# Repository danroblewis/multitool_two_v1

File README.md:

This was originally supposed to be 3 modules mashed together

But I'm bad at noise generator circuits

So I made a beat sequencer with flipflops

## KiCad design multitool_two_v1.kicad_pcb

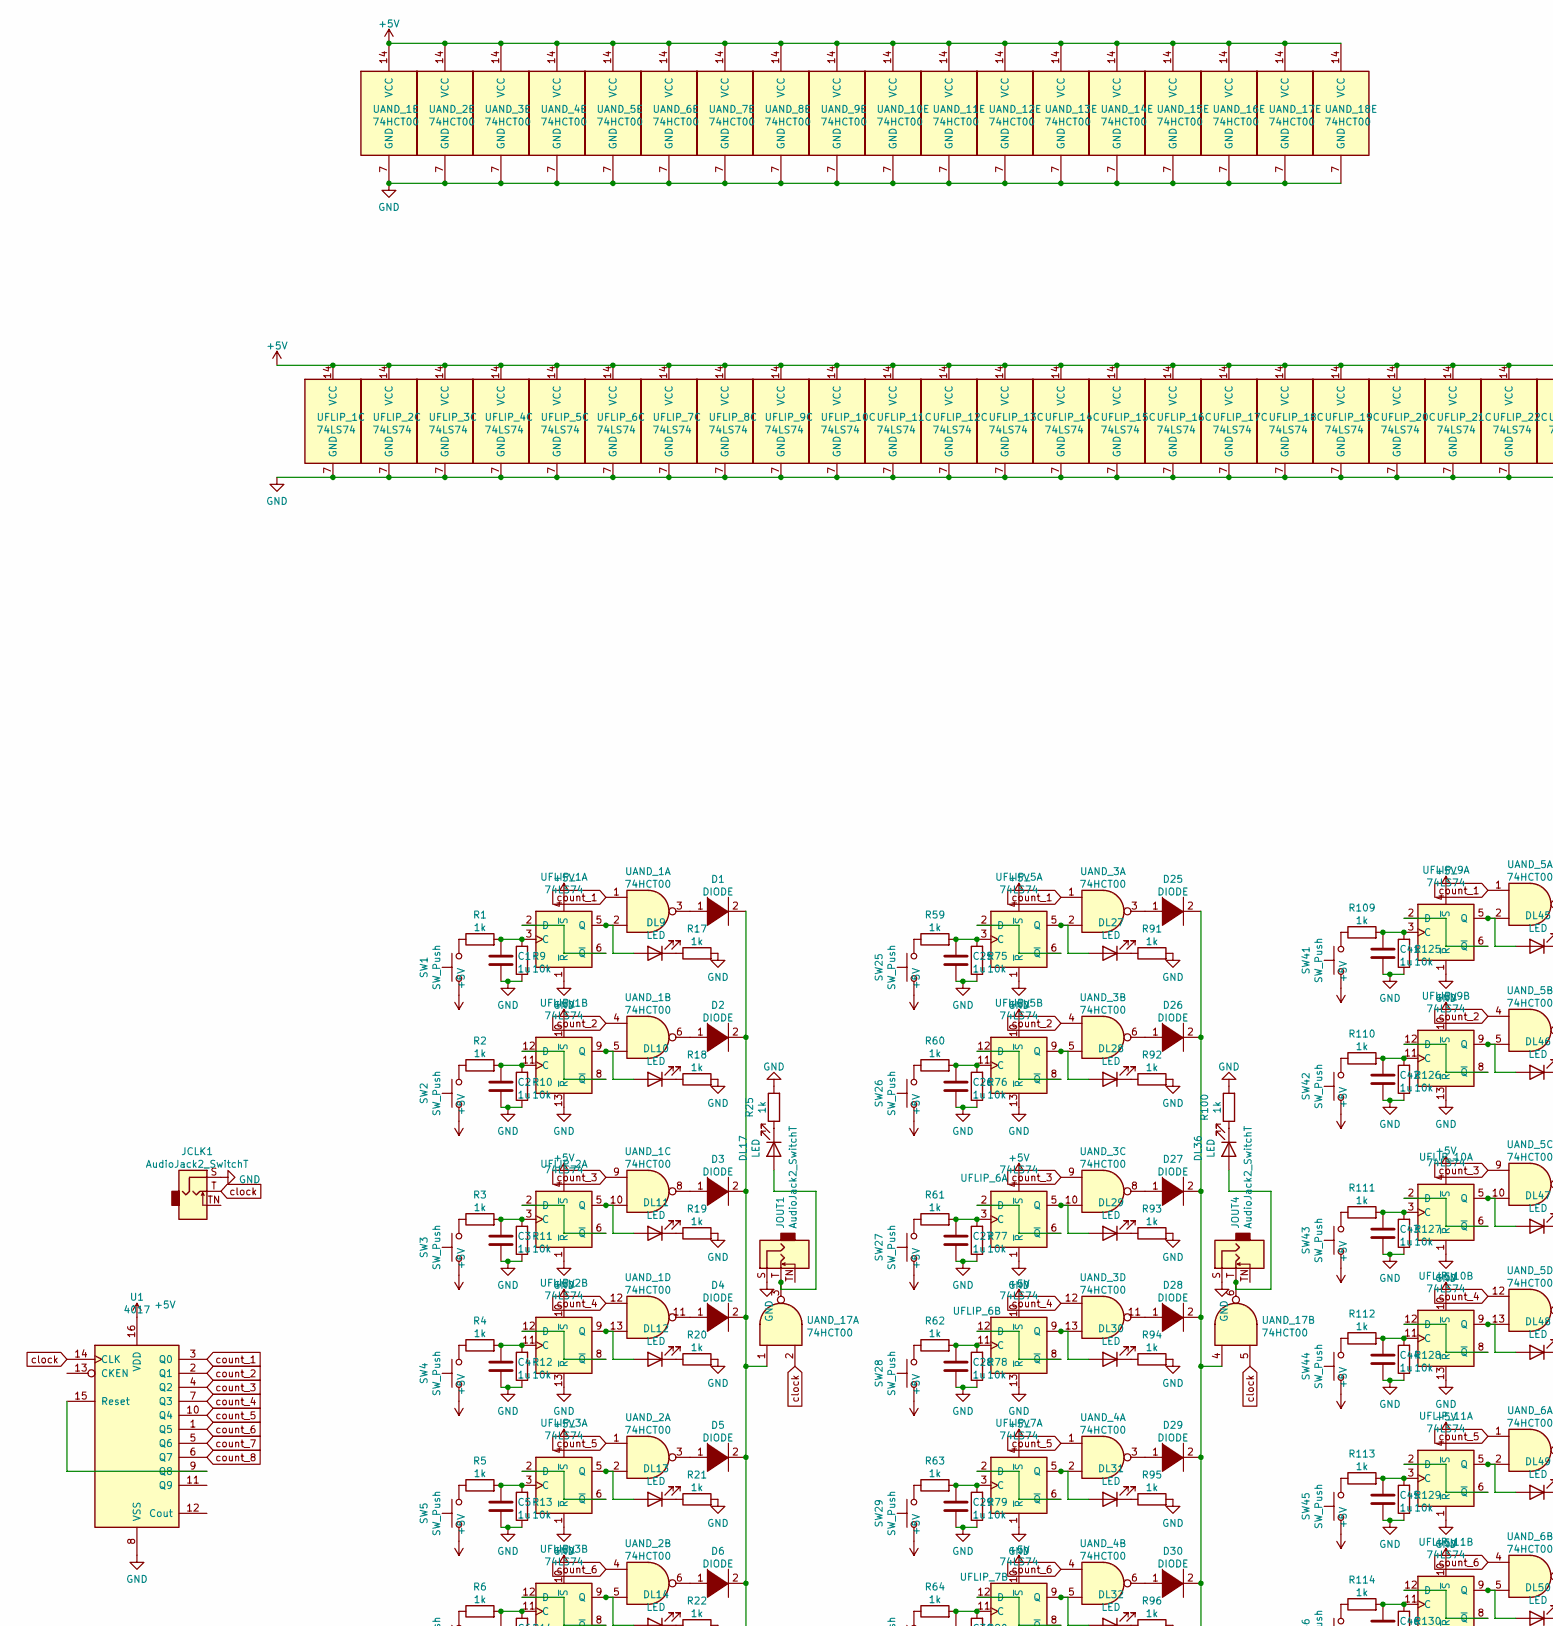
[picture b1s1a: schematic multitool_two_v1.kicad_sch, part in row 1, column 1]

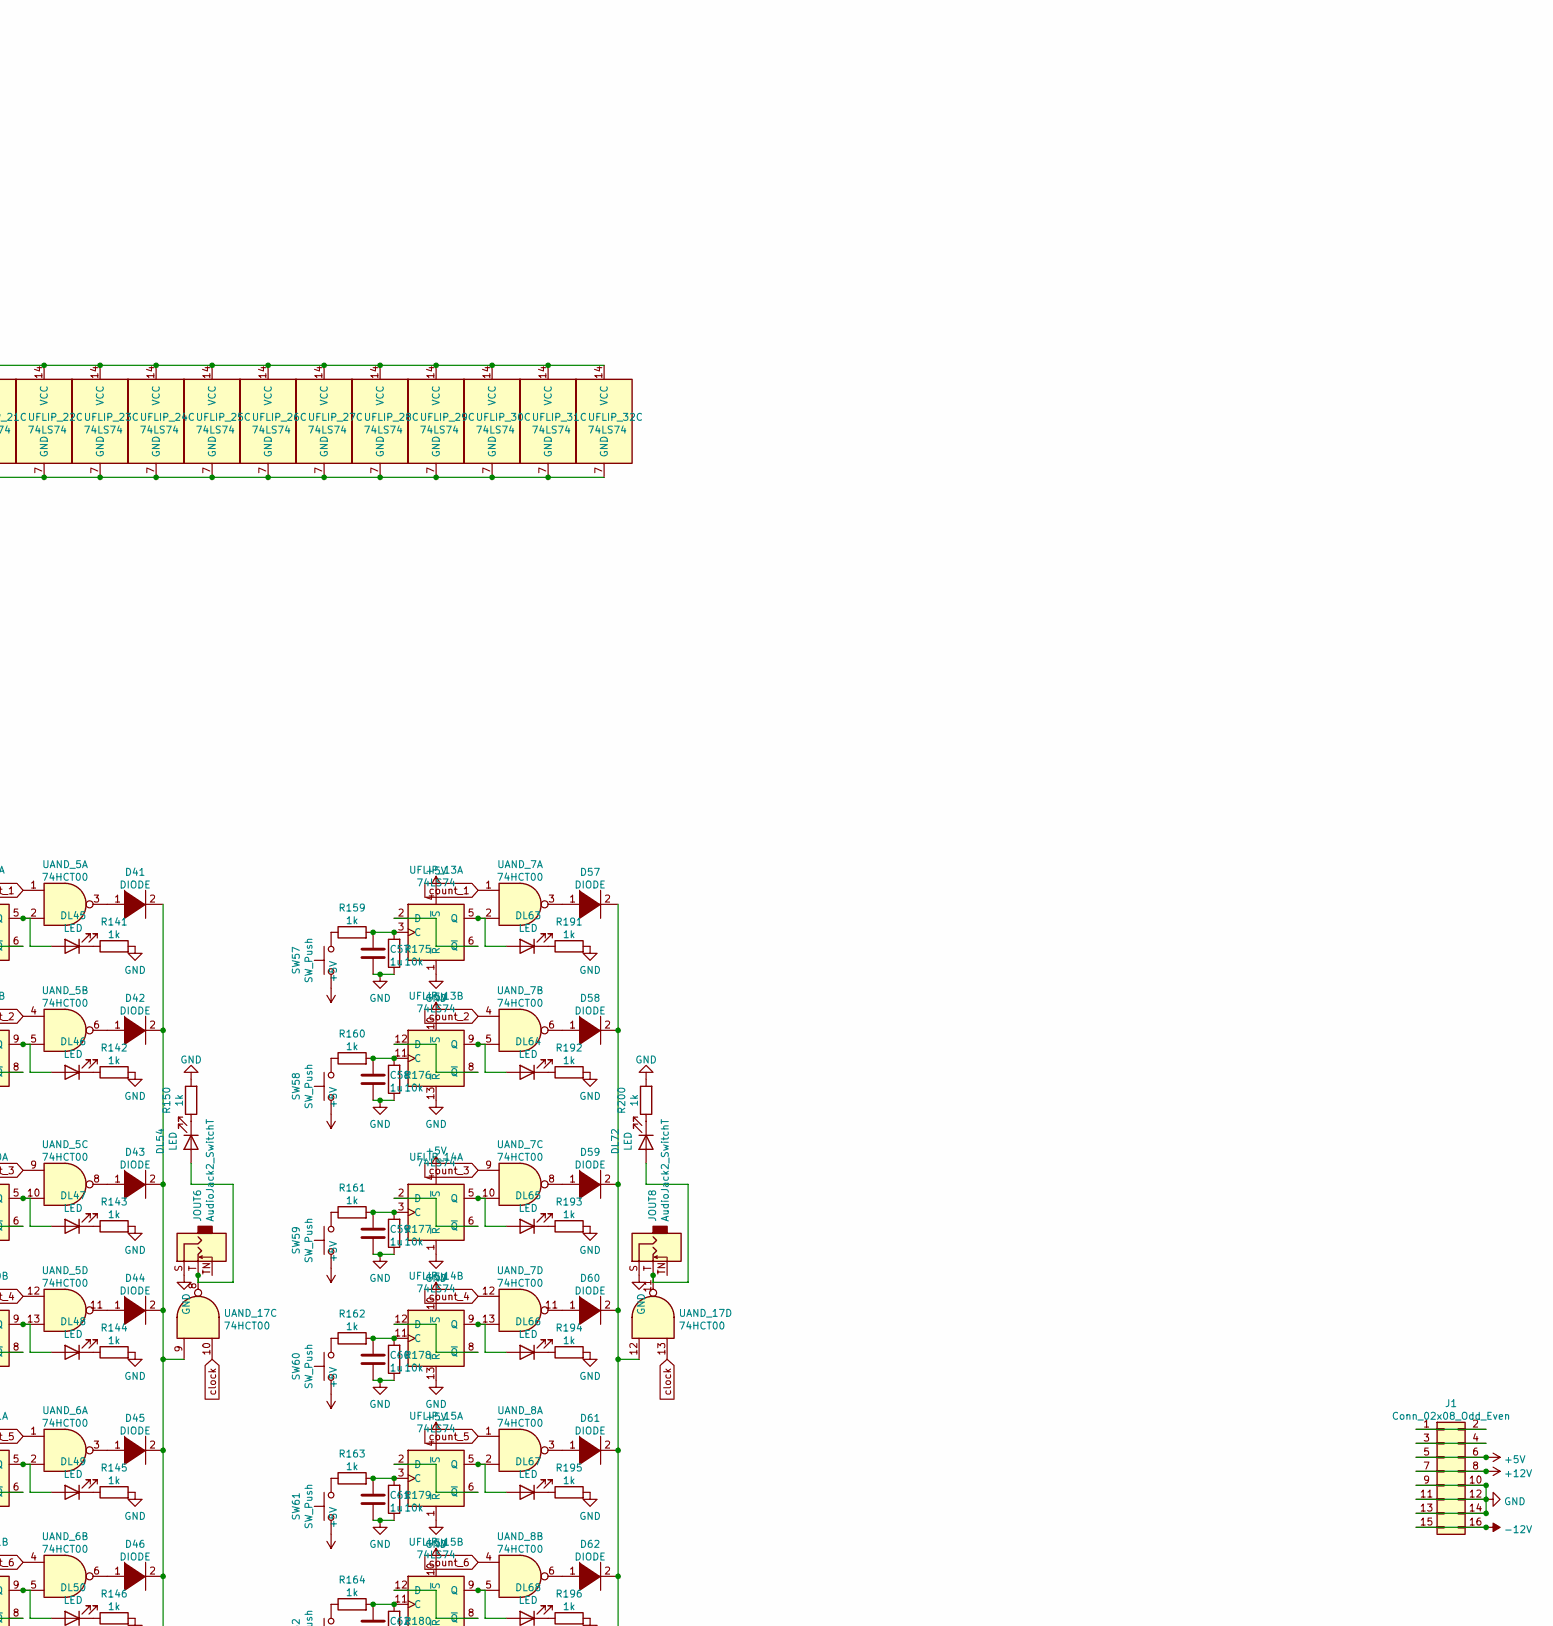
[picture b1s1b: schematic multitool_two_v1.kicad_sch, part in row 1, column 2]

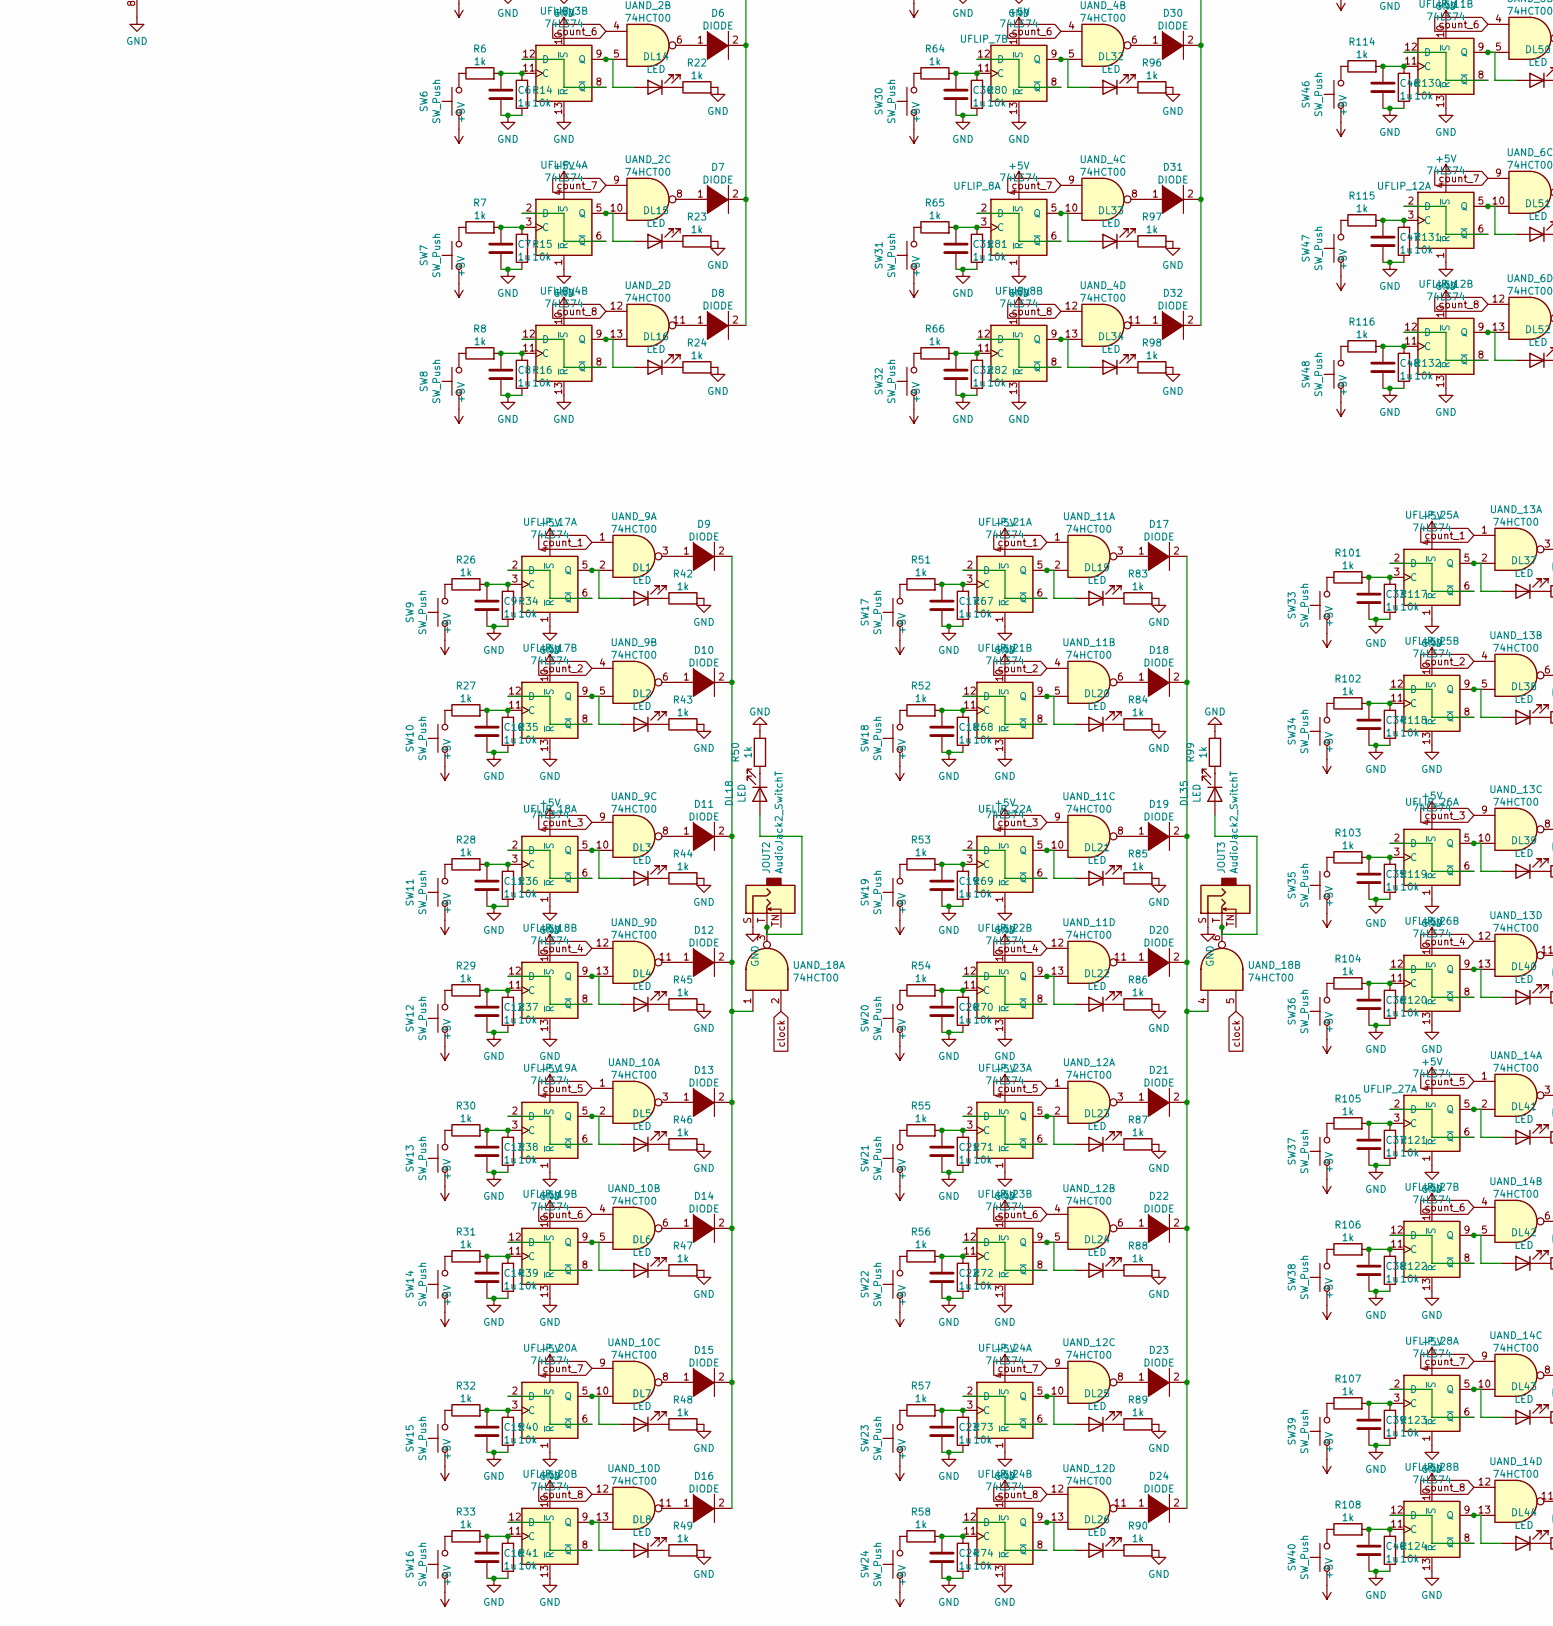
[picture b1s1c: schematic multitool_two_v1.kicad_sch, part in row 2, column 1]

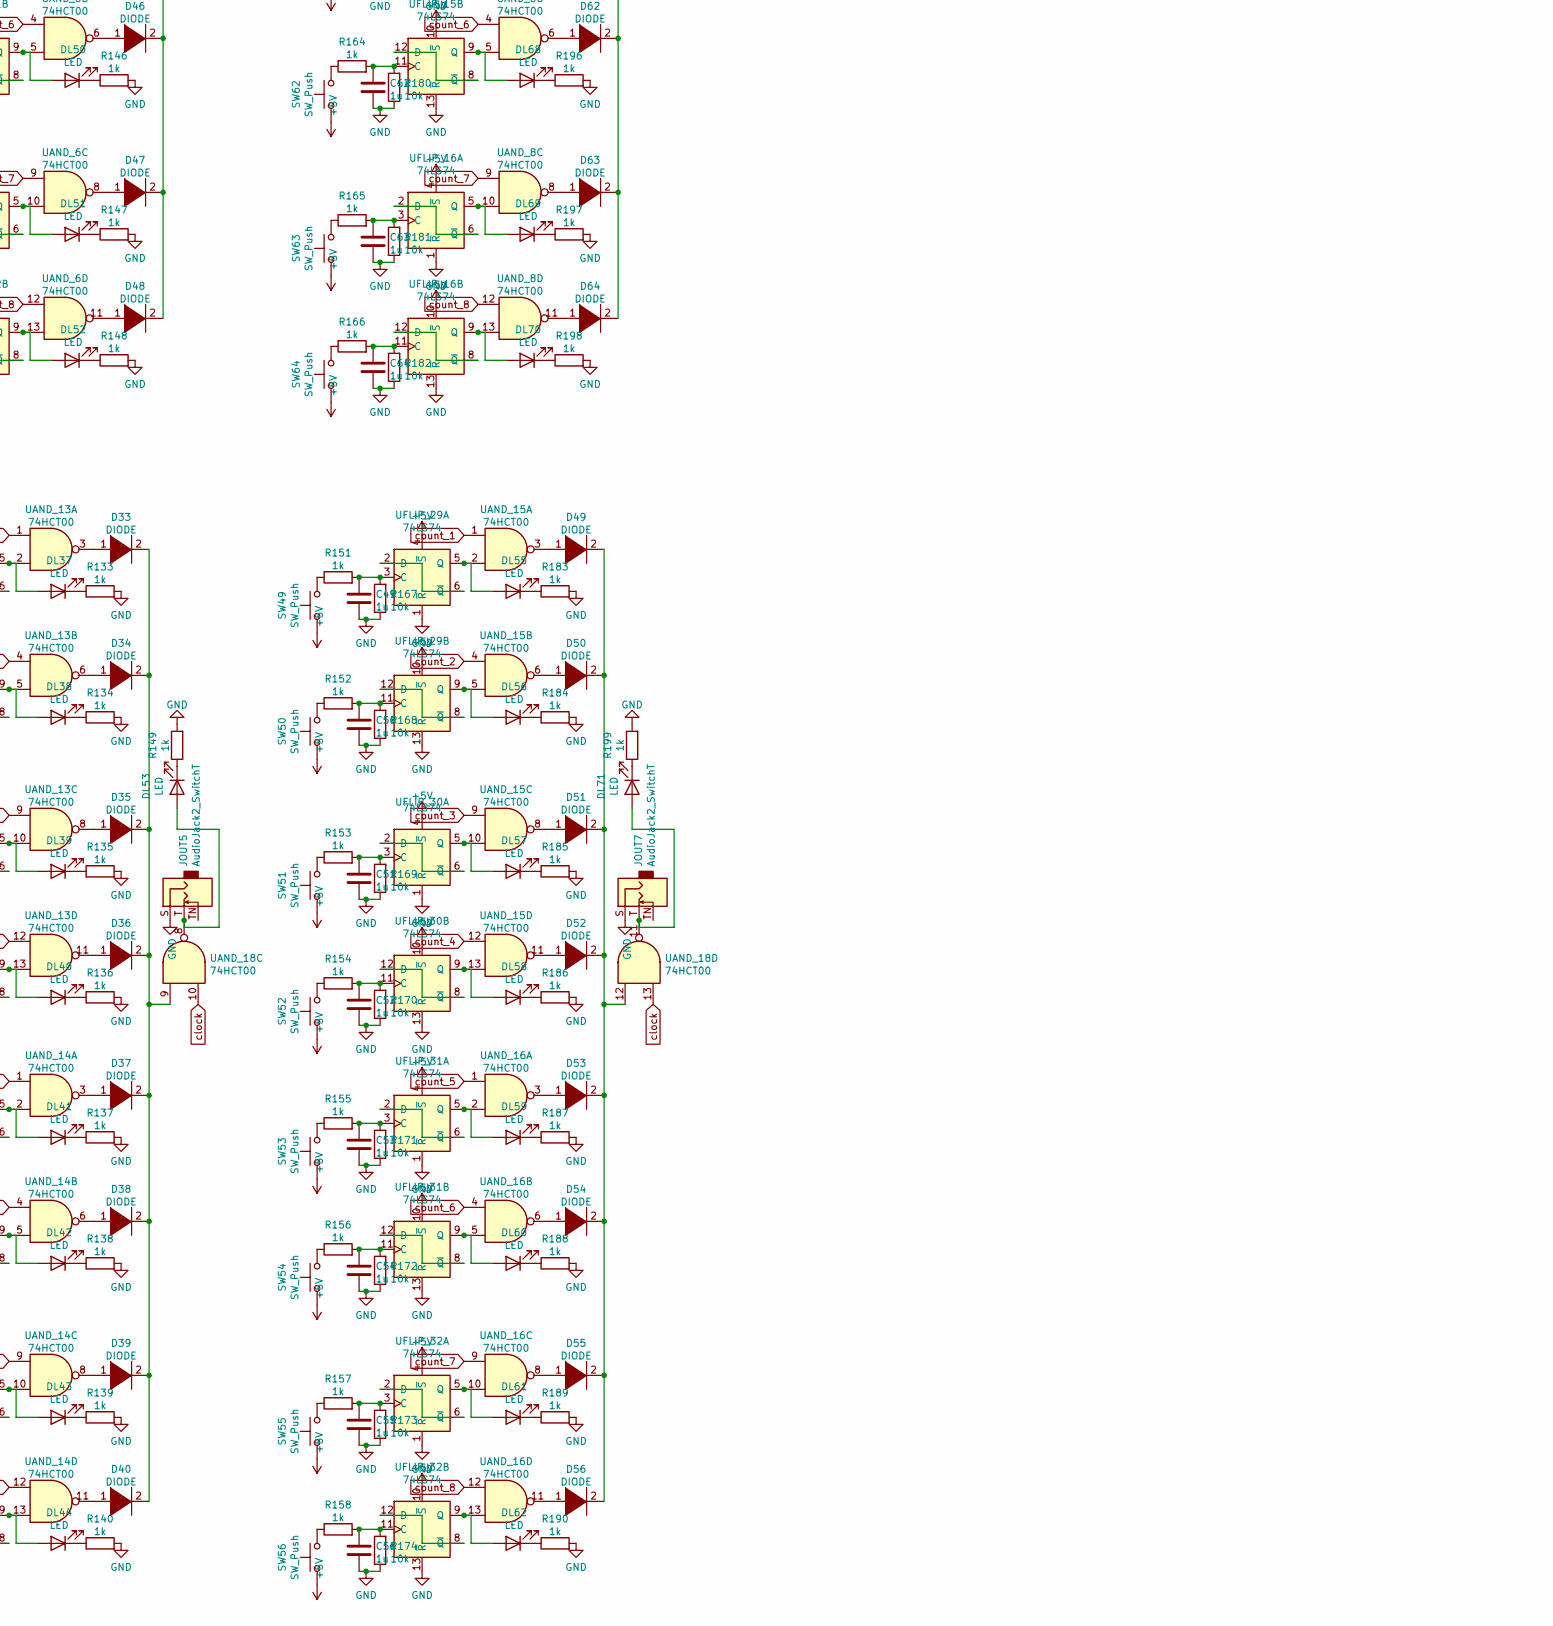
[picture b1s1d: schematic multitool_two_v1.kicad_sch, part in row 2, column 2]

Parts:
C1, C2, C3, C4, C5, C6, C7, C8, C9, C10, C11, C12, C13, C14, C15, C16, C17, C18, C19, C20, C21, C22, C23, C24, C25, C26, C27, C28, C29, C30, C31, C32, C33, C34, C35, C36, C37, C38, C39, C40, C41, C42, C43, C44, C45, C46, C47, C48, C49, C50, C51, C52, C53, C54, C55, C56, C57, C58, C59, C60, C61, C62, C63, C64: 1u; C_0603_1608Metric
D1, D2, D3, D4, D5, D6, D7, D8, D9, D10, D11, D12, D13, D14, D15, D16, D17, D18, D19, D20, D21, D22, D23, D24, D25, D26, D27, D28, D29, D30, D31, D32, D33, D34, D35, D36, D37, D38, D39, D40, D41, D42, D43, D44, D45, D46, D47, D48, D49, D50, D51, D52, D53, D54, D55, D56, D57, D58, D59, D60, D61, D62, D63, D64: DIODE; D_SOD-323F
DL1, DL2, DL3, DL4, DL5, DL6, DL7, DL8, DL9, DL10, DL11, DL12, DL13, DL14, DL15, DL16, DL17, DL18, DL19, DL20, DL21, DL22, DL23, DL24, DL25, DL26, DL27, DL28, DL29, DL30, DL31, DL32, DL33, DL34, DL35, DL36, DL37, DL38, DL39, DL40, DL41, DL42, DL43, DL44, DL45, DL46, DL47, DL48, DL49, DL50, DL51, DL52, DL53, DL54, DL55, DL56, DL57, DL58, DL59, DL60, DL61, DL62, DL63, DL64, DL65, DL66, DL67, DL68, DL69, DL70, DL71, DL72: LED; LED_0603_1608Metric
J1: Conn_02x08_Odd_Even; IDC-Header_2x08_P2.54mm_Vertical
JCLK1: AudioJack2_SwitchT; Jack_3.5mm_QingPu_WQP-PJ398SM_Vertical_CircularHoles
JOUT1, JOUT2, JOUT3, JOUT4, JOUT5, JOUT6, JOUT7, JOUT8: AudioJack2_SwitchT; Jack_3.5mm_QingPu_WQP-PJ398SM_Vertical_CircularHoles
R1, R2, R3, R4, R5, R6, R7, R8, R17, R18, R19, R20, R21, R22, R23, R24, R25, R26, R27, R28, R29, R30, R31, R32, R33, R42, R43, R44, R45, R46, R47, R48, R49, R50, R51, R52, R53, R54, R55, R56, R57, R58, R59, R60, R61, R62, R63, R64, R65, R66, R83, R84, R85, R86, R87, R88, R89, R90, R91, R92, R93, R94, R95, R96, R97, R98, R99, R100, R101, R102, R103, R104, R105, R106, R107, R108, R109, R110, R111, R112, R113, R114, R115, R116, R133, R134, R135, R136, R137, R138, R139, R140, R141, R142, R143, R144, R145, R146, R147, R148, R149, R150, R151, R152, R153, R154, R155, R156, R157, R158, R159, R160, R161, R162, R163, R164, R165, R166, R183, R184, R185, R186, R187, R188, R189, R190, R191, R192, R193, R194, R195, R196, R197, R198, R199, R200: 1k; R_0603_1608Metric
R9, R10, R11, R12, R13, R14, R15, R16, R34, R35, R36, R37, R38, R39, R40, R41, R67, R68, R69, R70, R71, R72, R73, R74, R75, R76, R77, R78, R79, R80, R81, R82, R117, R118, R119, R120, R121, R122, R123, R124, R125, R126, R127, R128, R129, R130, R131, R132, R167, R168, R169, R170, R171, R172, R173, R174, R175, R176, R177, R178, R179, R180, R181, R182: 10k; R_0603_1608Metric
SW1, SW2, SW3, SW4, SW5, SW6, SW7, SW8, SW9, SW10, SW11, SW12, SW13, SW14, SW15, SW16, SW17, SW18, SW19, SW20, SW21, SW22, SW23, SW24, SW25, SW26, SW27, SW28, SW29, SW30, SW31, SW32, SW33, SW34, SW35, SW36, SW37, SW38, SW39, SW40, SW41, SW42, SW43, SW44, SW45, SW46, SW47, SW48, SW49, SW50, SW51, SW52, SW53, SW54, SW55, SW56, SW57, SW58, SW59, SW60, SW61, SW62, SW63, SW64: SW_Push; SW_SPST_B3S-1000
U1: 4017; SOIC-16_3.9x9.9mm_P1.27mm
UAND_1, UAND_2, UAND_3, UAND_4, UAND_5, UAND_6, UAND_7, UAND_8, UAND_9, UAND_10, UAND_11, UAND_12, UAND_13, UAND_14, UAND_15, UAND_16, UAND_17, UAND_18: 74HCT00; SO-14_3.9x8.65mm_P1.27mm
UFLIP_1, UFLIP_2, UFLIP_3, UFLIP_4, UFLIP_5, UFLIP_6, UFLIP_7, UFLIP_8, UFLIP_9, UFLIP_10, UFLIP_11, UFLIP_12, UFLIP_13, UFLIP_14, UFLIP_15, UFLIP_16, UFLIP_17, UFLIP_18, UFLIP_19, UFLIP_20, UFLIP_21, UFLIP_22, UFLIP_23, UFLIP_24, UFLIP_25, UFLIP_26, UFLIP_27, UFLIP_28, UFLIP_29, UFLIP_30, UFLIP_31, UFLIP_32: 74LS74; SOIC-14_3.9x8.7mm_P1.27mm

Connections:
+5V: J1.5, J1.6, SW1.1, SW2.1, SW3.1, SW4.1, SW5.1, SW6.1, SW7.1, SW8.1, SW9.1, SW10.1, SW11.1, SW12.1, SW13.1, SW14.1, SW15.1, SW16.1, SW17.1, SW18.1, SW19.1, SW20.1, SW21.1, SW22.1, SW23.1, SW24.1, SW25.1, SW26.1, SW27.1, SW28.1, SW29.1, SW30.1, SW31.1, SW32.1, SW33.1, SW34.1, SW35.1, SW36.1, SW37.1, SW38.1, SW39.1, SW40.1, SW41.1, SW42.1, SW43.1, SW44.1, SW45.1, SW46.1, SW47.1, SW48.1, SW49.1, SW50.1, SW51.1, SW52.1, SW53.1, SW54.1, SW55.1, SW56.1, SW57.1, SW58.1, SW59.1, SW60.1, SW61.1, SW62.1, SW63.1, SW64.1, U1.16 (VDD), UAND_1.14 (VCC), UAND_2.14 (VCC), UAND_3.14 (VCC), UAND_4.14 (VCC), UAND_5.14 (VCC), UAND_6.14 (VCC), UAND_7.14 (VCC), UAND_8.14 (VCC), UAND_9.14 (VCC), UAND_10.14 (VCC), UAND_11.14 (VCC), UAND_12.14 (VCC), UAND_13.14 (VCC), UAND_14.14 (VCC), UAND_15.14 (VCC), UAND_16.14 (VCC), UAND_17.14 (VCC), UAND_18.14 (VCC), UFLIP_1.4 (~S), UFLIP_1.10 (~S), UFLIP_1.14 (VCC), UFLIP_2.4 (~S), UFLIP_2.10 (~S), UFLIP_2.14 (VCC), UFLIP_3.4 (~S), UFLIP_3.10 (~S), UFLIP_3.14 (VCC), UFLIP_4.4 (~S), UFLIP_4.10 (~S), UFLIP_4.14 (VCC), UFLIP_5.4 (~S), UFLIP_5.10 (~S), UFLIP_5.14 (VCC), UFLIP_6.4 (~S), UFLIP_6.10 (~S), UFLIP_6.14 (VCC), UFLIP_7.4 (~S), UFLIP_7.10 (~S), UFLIP_7.14 (VCC), UFLIP_8.4 (~S), UFLIP_8.10 (~S), UFLIP_8.14 (VCC), UFLIP_9.4 (~S), UFLIP_9.10 (~S), UFLIP_9.14 (VCC), UFLIP_10.4 (~S), UFLIP_10.10 (~S), UFLIP_10.14 (VCC)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
+12V: J1.7, J1.8
-12V: J1.15, J1.16
GND: C1.2, C2.2, C3.2, C4.2, C5.2, C6.2, C7.2, C8.2, C9.2, C10.2, C11.2, C12.2, C13.2, C14.2, C15.2, C16.2, C17.2, C18.2, C19.2, C20.2, C21.2, C22.2, C23.2, C24.2, C25.2, C26.2, C27.2, C28.2, C29.2, C30.2, C31.2, C32.2, C33.2, C34.2, C35.2, C36.2, C37.2, C38.2, C39.2, C40.2, C41.2, C42.2, C43.2, C44.2, C45.2, C46.2, C47.2, C48.2, C49.2, C50.2, C51.2, C52.2, C53.2, C54.2, C55.2, C56.2, C57.2, C58.2, C59.2, C60.2, C61.2, C62.2, C63.2, C64.2, J1.9, J1.10, J1.11, J1.12, J1.13, J1.14, JCLK1.S, JOUT1.S, JOUT2.S, JOUT3.S, JOUT4.S, JOUT5.S, JOUT6.S, JOUT7.S, JOUT8.S, R9.1, R10.1, R11.1, R12.1, R13.1, R14.1, R15.1, R16.1, R17.2, R18.2, R19.2, R20.2, R21.2, R22.2, R23.2, R24.2, R25.2, R34.1, R35.1, R36.1, R37.1, R38.1, R39.1, R40.1, R41.1, R42.2, R43.2, R44.2, R45.2, R46.2, R47.2, R48.2, R49.2, R50.2, R67.1, R68.1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
unnamed: C1.1, R1.2, R9.2, UFLIP_1.3 (C)
unnamed: C2.1, R2.2, R10.2, UFLIP_1.11 (C)
unnamed: C3.1, R3.2, R11.2, UFLIP_2.3 (C)
unnamed: C4.1, R4.2, R12.2, UFLIP_2.11 (C)
unnamed: C5.1, R5.2, R13.2, UFLIP_3.3 (C)
unnamed: C6.1, R6.2, R14.2, UFLIP_3.11 (C)
unnamed: C7.1, R7.2, R15.2, UFLIP_4.3 (C)
unnamed: C8.1, R8.2, R16.2, UFLIP_4.11 (C)
unnamed: C9.1, R26.2, R34.2, UFLIP_17.3 (C)
unnamed: C10.1, R27.2, R35.2, UFLIP_17.11 (C)
unnamed: C11.1, R28.2, R36.2, UFLIP_18.3 (C)
unnamed: C12.1, R29.2, R37.2, UFLIP_18.11 (C)
unnamed: C13.1, R30.2, R38.2, UFLIP_19.3 (C)
unnamed: C14.1, R31.2, R39.2, UFLIP_19.11 (C)
unnamed: C15.1, R32.2, R40.2, UFLIP_20.3 (C)
unnamed: C16.1, R33.2, R41.2, UFLIP_20.11 (C)
unnamed: C17.1, R51.2, R67.2, UFLIP_21.3 (C)
unnamed: C18.1, R52.2, R68.2, UFLIP_21.11 (C)
unnamed: C19.1, R53.2, R69.2, UFLIP_22.3 (C)
unnamed: C20.1, R54.2, R70.2, UFLIP_22.11 (C)
unnamed: C21.1, R55.2, R71.2, UFLIP_23.3 (C)
unnamed: C22.1, R56.2, R72.2, UFLIP_23.11 (C)
unnamed: C23.1, R57.2, R73.2, UFLIP_24.3 (C)
unnamed: C24.1, R58.2, R74.2, UFLIP_24.11 (C)
unnamed: C25.1, R59.2, R75.2, UFLIP_5.3 (C)
unnamed: C26.1, R60.2, R76.2, UFLIP_5.11 (C)
unnamed: C27.1, R61.2, R77.2, UFLIP_6.3 (C)
unnamed: C28.1, R62.2, R78.2, UFLIP_6.11 (C)
unnamed: C29.1, R63.2, R79.2, UFLIP_7.3 (C)
unnamed: C30.1, R64.2, R80.2, UFLIP_7.11 (C)
unnamed: C31.1, R65.2, R81.2, UFLIP_8.3 (C)
unnamed: C32.1, R66.2, R82.2, UFLIP_8.11 (C)
unnamed: C33.1, R101.2, R117.2, UFLIP_25.3 (C)
unnamed: C34.1, R102.2, R118.2, UFLIP_25.11 (C)
unnamed: C35.1, R103.2, R119.2, UFLIP_26.3 (C)
unnamed: C36.1, R104.2, R120.2, UFLIP_26.11 (C)
unnamed: C37.1, R105.2, R121.2, UFLIP_27.3 (C)
unnamed: C38.1, R106.2, R122.2, UFLIP_27.11 (C)
unnamed: C39.1, R107.2, R123.2, UFLIP_28.3 (C)
unnamed: C40.1, R108.2, R124.2, UFLIP_28.11 (C)
unnamed: C41.1, R109.2, R125.2, UFLIP_9.3 (C)
unnamed: C42.1, R110.2, R126.2, UFLIP_9.11 (C)
unnamed: C43.1, R111.2, R127.2, UFLIP_10.3 (C)
unnamed: C44.1, R112.2, R128.2, UFLIP_10.11 (C)
unnamed: C45.1, R113.2, R129.2, UFLIP_11.3 (C)
unnamed: C46.1, R114.2, R130.2, UFLIP_11.11 (C)
unnamed: C47.1, R115.2, R131.2, UFLIP_12.3 (C)
unnamed: C48.1, R116.2, R132.2, UFLIP_12.11 (C)
unnamed: C49.1, R151.2, R167.2, UFLIP_29.3 (C)
unnamed: C50.1, R152.2, R168.2, UFLIP_29.11 (C)
unnamed: C51.1, R153.2, R169.2, UFLIP_30.3 (C)
unnamed: C52.1, R154.2, R170.2, UFLIP_30.11 (C)
unnamed: C53.1, R155.2, R171.2, UFLIP_31.3 (C)
unnamed: C54.1, R156.2, R172.2, UFLIP_31.11 (C)
unnamed: C55.1, R157.2, R173.2, UFLIP_32.3 (C)
unnamed: C56.1, R158.2, R174.2, UFLIP_32.11 (C)
unnamed: C57.1, R159.2, R175.2, UFLIP_13.3 (C)
unnamed: C58.1, R160.2, R176.2, UFLIP_13.11 (C)
unnamed: C59.1, R161.2, R177.2, UFLIP_14.3 (C)
unnamed: C60.1, R162.2, R178.2, UFLIP_14.11 (C)
unnamed: C61.1, R163.2, R179.2, UFLIP_15.3 (C)
unnamed: C62.1, R164.2, R180.2, UFLIP_15.11 (C)
unnamed: C63.1, R165.2, R181.2, UFLIP_16.3 (C)
unnamed: C64.1, R166.2, R182.2, UFLIP_16.11 (C)
unnamed: D1.1 (K), UAND_1.3
unnamed: D1.2 (A), D2.2 (A), D3.2 (A), D4.2 (A), D5.2 (A), D6.2 (A), D7.2 (A), D8.2 (A), UAND_17.1
unnamed: D2.1 (K), UAND_1.6
unnamed: D3.1 (K), UAND_1.8
unnamed: D4.1 (K), UAND_1.11
unnamed: D5.1 (K), UAND_2.3
unnamed: D6.1 (K), UAND_2.6
unnamed: D7.1 (K), UAND_2.8
unnamed: D8.1 (K), UAND_2.11
unnamed: D9.1 (K), UAND_9.3
unnamed: D10.1 (K), UAND_9.6
unnamed: D9.2 (A), D10.2 (A), D11.2 (A), D12.2 (A), D13.2 (A), D14.2 (A), D15.2 (A), D16.2 (A), UAND_18.1
unnamed: D11.1 (K), UAND_9.8
unnamed: D12.1 (K), UAND_9.11
unnamed: D13.1 (K), UAND_10.3
unnamed: D14.1 (K), UAND_10.6
unnamed: D15.1 (K), UAND_10.8
unnamed: D16.1 (K), UAND_10.11
unnamed: D17.1 (K), UAND_11.3
unnamed: D17.2 (A), D18.2 (A), D19.2 (A), D20.2 (A), D21.2 (A), D22.2 (A), D23.2 (A), D24.2 (A), UAND_18.4
unnamed: D18.1 (K), UAND_11.6
unnamed: D19.1 (K), UAND_11.8
unnamed: D20.1 (K), UAND_11.11
unnamed: D21.1 (K), UAND_12.3
unnamed: D22.1 (K), UAND_12.6
unnamed: D23.1 (K), UAND_12.8
unnamed: D24.1 (K), UAND_12.11
unnamed: D25.1 (K), UAND_3.3
unnamed: D25.2 (A), D26.2 (A), D27.2 (A), D28.2 (A), D29.2 (A), D30.2 (A), D31.2 (A), D32.2 (A), UAND_17.4
unnamed: D26.1 (K), UAND_3.6
unnamed: D27.1 (K), UAND_3.8
unnamed: D28.1 (K), UAND_3.11
unnamed: D29.1 (K), UAND_4.3
unnamed: D30.1 (K), UAND_4.6
unnamed: D31.1 (K), UAND_4.8
unnamed: D32.1 (K), UAND_4.11
unnamed: D33.1 (K), UAND_13.3
unnamed: D33.2 (A), D34.2 (A), D35.2 (A), D36.2 (A), D37.2 (A), D38.2 (A), D39.2 (A), D40.2 (A), UAND_18.9
unnamed: D34.1 (K), UAND_13.6
unnamed: D35.1 (K), UAND_13.8
unnamed: D36.1 (K), UAND_13.11
unnamed: D37.1 (K), UAND_14.3
unnamed: D38.1 (K), UAND_14.6
unnamed: D39.1 (K), UAND_14.8
unnamed: D40.1 (K), UAND_14.11
unnamed: D41.1 (K), UAND_5.3
unnamed: D41.2 (A), D42.2 (A), D43.2 (A), D44.2 (A), D45.2 (A), D46.2 (A), D47.2 (A), D48.2 (A), UAND_17.9
unnamed: D42.1 (K), UAND_5.6
unnamed: D43.1 (K), UAND_5.8
unnamed: D44.1 (K), UAND_5.11
unnamed: D45.1 (K), UAND_6.3
unnamed: D46.1 (K), UAND_6.6
unnamed: D47.1 (K), UAND_6.8
unnamed: D48.1 (K), UAND_6.11
unnamed: D49.1 (K), UAND_15.3
unnamed: D49.2 (A), D50.2 (A), D51.2 (A), D52.2 (A), D53.2 (A), D54.2 (A), D55.2 (A), D56.2 (A), UAND_18.12
unnamed: D50.1 (K), UAND_15.6
unnamed: D51.1 (K), UAND_15.8
unnamed: D52.1 (K), UAND_15.11
unnamed: D53.1 (K), UAND_16.3
unnamed: D54.1 (K), UAND_16.6
unnamed: D55.1 (K), UAND_16.8
unnamed: D56.1 (K), UAND_16.11
unnamed: D57.1 (K), UAND_7.3
unnamed: D57.2 (A), D58.2 (A), D59.2 (A), D60.2 (A), D61.2 (A), D62.2 (A), D63.2 (A), D64.2 (A), UAND_17.12
unnamed: D58.1 (K), UAND_7.6
unnamed: D59.1 (K), UAND_7.8
unnamed: D60.1 (K), UAND_7.11
unnamed: D61.1 (K), UAND_8.3
unnamed: D62.1 (K), UAND_8.6
unnamed: D63.1 (K), UAND_8.8
unnamed: D64.1 (K), UAND_8.11
unnamed: DL1.1 (K), R42.1
unnamed: DL1.2 (A), UAND_9.2, UFLIP_17.5 (Q)
unnamed: DL2.1 (K), R43.1
unnamed: DL2.2 (A), UAND_9.5, UFLIP_17.9 (Q)
unnamed: DL3.1 (K), R44.1
unnamed: DL3.2 (A), UAND_9.10, UFLIP_18.5 (Q)
unnamed: DL4.1 (K), R45.1
unnamed: DL4.2 (A), UAND_9.13, UFLIP_18.9 (Q)
unnamed: DL5.1 (K), R46.1
unnamed: DL5.2 (A), UAND_10.2, UFLIP_19.5 (Q)
unnamed: DL6.1 (K), R47.1
unnamed: DL6.2 (A), UAND_10.5, UFLIP_19.9 (Q)
unnamed: DL7.1 (K), R48.1
unnamed: DL7.2 (A), UAND_10.10, UFLIP_20.5 (Q)
unnamed: DL8.1 (K), R49.1
unnamed: DL8.2 (A), UAND_10.13, UFLIP_20.9 (Q)
unnamed: DL9.1 (K), R17.1
unnamed: DL9.2 (A), UAND_1.2, UFLIP_1.5 (Q)
unnamed: DL10.1 (K), R18.1
unnamed: DL10.2 (A), UAND_1.5, UFLIP_1.9 (Q)
unnamed: DL11.1 (K), R19.1
unnamed: DL11.2 (A), UAND_1.10, UFLIP_2.5 (Q)
unnamed: DL12.1 (K), R20.1
unnamed: DL12.2 (A), UAND_1.13, UFLIP_2.9 (Q)
unnamed: DL13.1 (K), R21.1
unnamed: DL13.2 (A), UAND_2.2, UFLIP_3.5 (Q)
unnamed: DL14.1 (K), R22.1
unnamed: DL14.2 (A), UAND_2.5, UFLIP_3.9 (Q)
unnamed: DL15.1 (K), R23.1
unnamed: DL15.2 (A), UAND_2.10, UFLIP_4.5 (Q)
unnamed: DL16.1 (K), R24.1
unnamed: DL16.2 (A), UAND_2.13, UFLIP_4.9 (Q)
unnamed: DL17.1 (K), R25.1
unnamed: DL17.2 (A), JOUT1.T, UAND_17.3
unnamed: DL18.1 (K), R50.1
unnamed: DL18.2 (A), JOUT2.T, UAND_18.3
unnamed: DL19.1 (K), R83.1
unnamed: DL19.2 (A), UAND_11.2, UFLIP_21.5 (Q)
unnamed: DL20.1 (K), R84.1
unnamed: DL20.2 (A), UAND_11.5, UFLIP_21.9 (Q)
unnamed: DL21.1 (K), R85.1
unnamed: DL21.2 (A), UAND_11.10, UFLIP_22.5 (Q)
unnamed: DL22.1 (K), R86.1
unnamed: DL22.2 (A), UAND_11.13, UFLIP_22.9 (Q)
unnamed: DL23.1 (K), R87.1
unnamed: DL23.2 (A), UAND_12.2, UFLIP_23.5 (Q)
unnamed: DL24.1 (K), R88.1
unnamed: DL24.2 (A), UAND_12.5, UFLIP_23.9 (Q)
unnamed: DL25.1 (K), R89.1
unnamed: DL25.2 (A), UAND_12.10, UFLIP_24.5 (Q)
unnamed: DL26.1 (K), R90.1
unnamed: DL26.2 (A), UAND_12.13, UFLIP_24.9 (Q)
unnamed: DL27.1 (K), R91.1
unnamed: DL27.2 (A), UAND_3.2, UFLIP_5.5 (Q)
unnamed: DL28.1 (K), R92.1
unnamed: DL28.2 (A), UAND_3.5, UFLIP_5.9 (Q)
unnamed: DL29.1 (K), R93.1
unnamed: DL29.2 (A), UAND_3.10, UFLIP_6.5 (Q)
unnamed: DL30.1 (K), R94.1
unnamed: DL30.2 (A), UAND_3.13, UFLIP_6.9 (Q)
unnamed: DL31.1 (K), R95.1
unnamed: DL31.2 (A), UAND_4.2, UFLIP_7.5 (Q)
unnamed: DL32.1 (K), R96.1
unnamed: DL32.2 (A), UAND_4.5, UFLIP_7.9 (Q)
unnamed: DL33.1 (K), R97.1
unnamed: DL33.2 (A), UAND_4.10, UFLIP_8.5 (Q)
unnamed: DL34.1 (K), R98.1
unnamed: DL34.2 (A), UAND_4.13, UFLIP_8.9 (Q)
unnamed: DL35.1 (K), R99.1
unnamed: DL35.2 (A), JOUT3.T, UAND_18.6
unnamed: DL36.1 (K), R100.1
unnamed: DL36.2 (A), JOUT4.T, UAND_17.6
unnamed: DL37.1 (K), R133.1
unnamed: DL37.2 (A), UAND_13.2, UFLIP_25.5 (Q)
unnamed: DL38.1 (K), R134.1
unnamed: DL38.2 (A), UAND_13.5, UFLIP_25.9 (Q)
unnamed: DL39.1 (K), R135.1
unnamed: DL39.2 (A), UAND_13.10, UFLIP_26.5 (Q)
unnamed: DL40.1 (K), R136.1
unnamed: DL40.2 (A), UAND_13.13, UFLIP_26.9 (Q)
unnamed: DL41.1 (K), R137.1
unnamed: DL41.2 (A), UAND_14.2, UFLIP_27.5 (Q)
unnamed: DL42.1 (K), R138.1
unnamed: DL42.2 (A), UAND_14.5, UFLIP_27.9 (Q)
unnamed: DL43.1 (K), R139.1
unnamed: DL43.2 (A), UAND_14.10, UFLIP_28.5 (Q)
unnamed: DL44.1 (K), R140.1
unnamed: DL44.2 (A), UAND_14.13, UFLIP_28.9 (Q)
unnamed: DL45.1 (K), R141.1
unnamed: DL45.2 (A), UAND_5.2, UFLIP_9.5 (Q)
unnamed: DL46.1 (K), R142.1
unnamed: DL46.2 (A), UAND_5.5, UFLIP_9.9 (Q)
unnamed: DL47.1 (K), R143.1
unnamed: DL47.2 (A), UAND_5.10, UFLIP_10.5 (Q)
unnamed: DL48.1 (K), R144.1
unnamed: DL48.2 (A), UAND_5.13, UFLIP_10.9 (Q)
unnamed: DL49.1 (K), R145.1
unnamed: DL49.2 (A), UAND_6.2, UFLIP_11.5 (Q)
unnamed: DL50.1 (K), R146.1
unnamed: DL50.2 (A), UAND_6.5, UFLIP_11.9 (Q)
unnamed: DL51.1 (K), R147.1
unnamed: DL51.2 (A), UAND_6.10, UFLIP_12.5 (Q)
unnamed: DL52.1 (K), R148.1
unnamed: DL52.2 (A), UAND_6.13, UFLIP_12.9 (Q)
unnamed: DL53.1 (K), R149.1
unnamed: DL53.2 (A), JOUT5.T, UAND_18.8
unnamed: DL54.1 (K), R150.1
unnamed: DL54.2 (A), JOUT6.T, UAND_17.8
unnamed: DL55.1 (K), R183.1
unnamed: DL55.2 (A), UAND_15.2, UFLIP_29.5 (Q)
unnamed: DL56.1 (K), R184.1
unnamed: DL56.2 (A), UAND_15.5, UFLIP_29.9 (Q)
unnamed: DL57.1 (K), R185.1
unnamed: DL57.2 (A), UAND_15.10, UFLIP_30.5 (Q)
unnamed: DL58.1 (K), R186.1
unnamed: DL58.2 (A), UAND_15.13, UFLIP_30.9 (Q)
unnamed: DL59.1 (K), R187.1
unnamed: DL59.2 (A), UAND_16.2, UFLIP_31.5 (Q)
unnamed: DL60.1 (K), R188.1
unnamed: DL60.2 (A), UAND_16.5, UFLIP_31.9 (Q)
unnamed: DL61.1 (K), R189.1
unnamed: DL61.2 (A), UAND_16.10, UFLIP_32.5 (Q)
unnamed: DL62.1 (K), R190.1
unnamed: DL62.2 (A), UAND_16.13, UFLIP_32.9 (Q)
unnamed: DL63.1 (K), R191.1
unnamed: DL63.2 (A), UAND_7.2, UFLIP_13.5 (Q)
unnamed: DL64.1 (K), R192.1
unnamed: DL64.2 (A), UAND_7.5, UFLIP_13.9 (Q)
unnamed: DL65.1 (K), R193.1
unnamed: DL65.2 (A), UAND_7.10, UFLIP_14.5 (Q)
unnamed: DL66.1 (K), R194.1
unnamed: DL66.2 (A), UAND_7.13, UFLIP_14.9 (Q)
unnamed: DL67.1 (K), R195.1
unnamed: DL67.2 (A), UAND_8.2, UFLIP_15.5 (Q)
unnamed: DL68.1 (K), R196.1
unnamed: DL68.2 (A), UAND_8.5, UFLIP_15.9 (Q)
unnamed: DL69.1 (K), R197.1
unnamed: DL69.2 (A), UAND_8.10, UFLIP_16.5 (Q)
unnamed: DL70.1 (K), R198.1
unnamed: DL70.2 (A), UAND_8.13, UFLIP_16.9 (Q)
unnamed: DL71.1 (K), R199.1
unnamed: DL71.2 (A), JOUT7.T, UAND_18.11
unnamed: DL72.1 (K), R200.1
unnamed: DL72.2 (A), JOUT8.T, UAND_17.11
unnamed: J1.1, J1.2
unnamed: J1.3, J1.4
unnamed: R1.1, SW1.2
unnamed: R2.1, SW2.2
unnamed: R3.1, SW3.2
unnamed: R4.1, SW4.2
unnamed: R5.1, SW5.2
unnamed: R6.1, SW6.2
unnamed: R7.1, SW7.2
unnamed: R8.1, SW8.2
unnamed: R26.1, SW9.2
unnamed: R27.1, SW10.2
unnamed: R28.1, SW11.2
unnamed: R29.1, SW12.2
unnamed: R30.1, SW13.2
unnamed: R31.1, SW14.2
unnamed: R32.1, SW15.2
unnamed: R33.1, SW16.2
unnamed: R51.1, SW17.2
unnamed: R52.1, SW18.2
unnamed: R53.1, SW19.2
unnamed: R54.1, SW20.2
unnamed: R55.1, SW21.2
unnamed: R56.1, SW22.2
unnamed: R57.1, SW23.2
unnamed: R58.1, SW24.2
unnamed: R59.1, SW25.2
unnamed: R60.1, SW26.2
unnamed: R61.1, SW27.2
unnamed: R62.1, SW28.2
unnamed: R63.1, SW29.2
unnamed: R64.1, SW30.2
unnamed: R65.1, SW31.2
unnamed: R66.1, SW32.2
unnamed: R101.1, SW33.2
unnamed: R102.1, SW34.2
unnamed: R103.1, SW35.2
unnamed: R104.1, SW36.2
unnamed: R105.1, SW37.2
unnamed: R106.1, SW38.2
unnamed: R107.1, SW39.2
unnamed: R108.1, SW40.2
unnamed: R109.1, SW41.2
unnamed: R110.1, SW42.2
unnamed: R111.1, SW43.2
unnamed: R112.1, SW44.2
unnamed: R113.1, SW45.2
unnamed: R114.1, SW46.2
unnamed: R115.1, SW47.2
unnamed: R116.1, SW48.2
unnamed: R151.1, SW49.2
unnamed: R152.1, SW50.2
unnamed: R153.1, SW51.2
unnamed: R154.1, SW52.2
unnamed: R155.1, SW53.2
unnamed: R156.1, SW54.2
unnamed: R157.1, SW55.2
unnamed: R158.1, SW56.2
unnamed: R159.1, SW57.2
unnamed: R160.1, SW58.2
unnamed: R161.1, SW59.2
unnamed: R162.1, SW60.2
unnamed: R163.1, SW61.2
unnamed: R164.1, SW62.2
unnamed: R165.1, SW63.2
unnamed: R166.1, SW64.2
unnamed: U1.9 (Q8), U1.15 (Reset)
unnamed: UFLIP_1.2 (D), UFLIP_1.6 (~Q)
unnamed: UFLIP_1.8 (~Q), UFLIP_1.12 (D)
unnamed: UFLIP_2.2 (D), UFLIP_2.6 (~Q)
unnamed: UFLIP_2.8 (~Q), UFLIP_2.12 (D)
unnamed: UFLIP_3.2 (D), UFLIP_3.6 (~Q)
unnamed: UFLIP_3.8 (~Q), UFLIP_3.12 (D)
unnamed: UFLIP_4.2 (D), UFLIP_4.6 (~Q)
unnamed: UFLIP_4.8 (~Q), UFLIP_4.12 (D)
unnamed: UFLIP_5.2 (D), UFLIP_5.6 (~Q)
unnamed: UFLIP_5.8 (~Q), UFLIP_5.12 (D)
unnamed: UFLIP_6.2 (D), UFLIP_6.6 (~Q)
unnamed: UFLIP_6.8 (~Q), UFLIP_6.12 (D)
unnamed: UFLIP_7.2 (D), UFLIP_7.6 (~Q)
unnamed: UFLIP_7.8 (~Q), UFLIP_7.12 (D)
unnamed: UFLIP_8.2 (D), UFLIP_8.6 (~Q)
unnamed: UFLIP_8.8 (~Q), UFLIP_8.12 (D)
unnamed: UFLIP_9.2 (D), UFLIP_9.6 (~Q)
unnamed: UFLIP_9.8 (~Q), UFLIP_9.12 (D)
unnamed: UFLIP_10.2 (D), UFLIP_10.6 (~Q)
unnamed: UFLIP_10.8 (~Q), UFLIP_10.12 (D)
unnamed: UFLIP_11.2 (D), UFLIP_11.6 (~Q)
unnamed: UFLIP_11.8 (~Q), UFLIP_11.12 (D)
unnamed: UFLIP_12.2 (D), UFLIP_12.6 (~Q)
unnamed: UFLIP_12.8 (~Q), UFLIP_12.12 (D)
unnamed: UFLIP_13.2 (D), UFLIP_13.6 (~Q)
unnamed: UFLIP_13.8 (~Q), UFLIP_13.12 (D)
unnamed: UFLIP_14.2 (D), UFLIP_14.6 (~Q)
unnamed: UFLIP_14.8 (~Q), UFLIP_14.12 (D)
unnamed: UFLIP_15.2 (D), UFLIP_15.6 (~Q)
unnamed: UFLIP_15.8 (~Q), UFLIP_15.12 (D)
unnamed: UFLIP_16.2 (D), UFLIP_16.6 (~Q)
unnamed: UFLIP_16.8 (~Q), UFLIP_16.12 (D)
unnamed: UFLIP_17.2 (D), UFLIP_17.6 (~Q)
unnamed: UFLIP_17.8 (~Q), UFLIP_17.12 (D)
unnamed: UFLIP_18.2 (D), UFLIP_18.6 (~Q)
unnamed: UFLIP_18.8 (~Q), UFLIP_18.12 (D)
unnamed: UFLIP_19.2 (D), UFLIP_19.6 (~Q)
unnamed: UFLIP_19.8 (~Q), UFLIP_19.12 (D)
unnamed: UFLIP_20.2 (D), UFLIP_20.6 (~Q)
unnamed: UFLIP_20.8 (~Q), UFLIP_20.12 (D)
unnamed: UFLIP_21.2 (D), UFLIP_21.6 (~Q)
unnamed: UFLIP_21.8 (~Q), UFLIP_21.12 (D)
unnamed: UFLIP_22.2 (D), UFLIP_22.6 (~Q)
unnamed: UFLIP_22.8 (~Q), UFLIP_22.12 (D)
unnamed: UFLIP_23.2 (D), UFLIP_23.6 (~Q)
unnamed: UFLIP_23.8 (~Q), UFLIP_23.12 (D)
unnamed: UFLIP_24.2 (D), UFLIP_24.6 (~Q)
unnamed: UFLIP_24.8 (~Q), UFLIP_24.12 (D)
unnamed: UFLIP_25.2 (D), UFLIP_25.6 (~Q)
unnamed: UFLIP_25.8 (~Q), UFLIP_25.12 (D)
unnamed: UFLIP_26.2 (D), UFLIP_26.6 (~Q)
unnamed: UFLIP_26.8 (~Q), UFLIP_26.12 (D)
unnamed: UFLIP_27.2 (D), UFLIP_27.6 (~Q)
unnamed: UFLIP_27.8 (~Q), UFLIP_27.12 (D)
unnamed: UFLIP_28.2 (D), UFLIP_28.6 (~Q)
unnamed: UFLIP_28.8 (~Q), UFLIP_28.12 (D)
unnamed: UFLIP_29.2 (D), UFLIP_29.6 (~Q)
unnamed: UFLIP_29.8 (~Q), UFLIP_29.12 (D)
unnamed: UFLIP_30.2 (D), UFLIP_30.6 (~Q)
unnamed: UFLIP_30.8 (~Q), UFLIP_30.12 (D)
unnamed: UFLIP_31.2 (D), UFLIP_31.6 (~Q)
unnamed: UFLIP_31.8 (~Q), UFLIP_31.12 (D)
unnamed: UFLIP_32.2 (D), UFLIP_32.6 (~Q)
unnamed: UFLIP_32.8 (~Q), UFLIP_32.12 (D)
clock: JCLK1.T, U1.14 (CLK), UAND_17.2, UAND_17.5, UAND_17.10, UAND_17.13, UAND_18.2, UAND_18.5, UAND_18.10, UAND_18.13
count_1: U1.3 (Q0), UAND_1.1, UAND_3.1, UAND_5.1, UAND_7.1, UAND_9.1, UAND_11.1, UAND_13.1, UAND_15.1
count_2: U1.2 (Q1), UAND_1.4, UAND_3.4, UAND_5.4, UAND_7.4, UAND_9.4, UAND_11.4, UAND_13.4, UAND_15.4
count_3: U1.4 (Q2), UAND_1.9, UAND_3.9, UAND_5.9, UAND_7.9, UAND_9.9, UAND_11.9, UAND_13.9, UAND_15.9
count_4: U1.7 (Q3), UAND_1.12, UAND_3.12, UAND_5.12, UAND_7.12, UAND_9.12, UAND_11.12, UAND_13.12, UAND_15.12
count_5: U1.10 (Q4), UAND_2.1, UAND_4.1, UAND_6.1, UAND_8.1, UAND_10.1, UAND_12.1, UAND_14.1, UAND_16.1
count_6: U1.1 (Q5), UAND_2.4, UAND_4.4, UAND_6.4, UAND_8.4, UAND_10.4, UAND_12.4, UAND_14.4, UAND_16.4
count_7: U1.5 (Q6), UAND_2.9, UAND_4.9, UAND_6.9, UAND_8.9, UAND_10.9, UAND_12.9, UAND_14.9, UAND_16.9
count_8: U1.6 (Q7), UAND_2.12, UAND_4.12, UAND_6.12, UAND_8.12, UAND_10.12, UAND_12.12, UAND_14.12, UAND_16.12

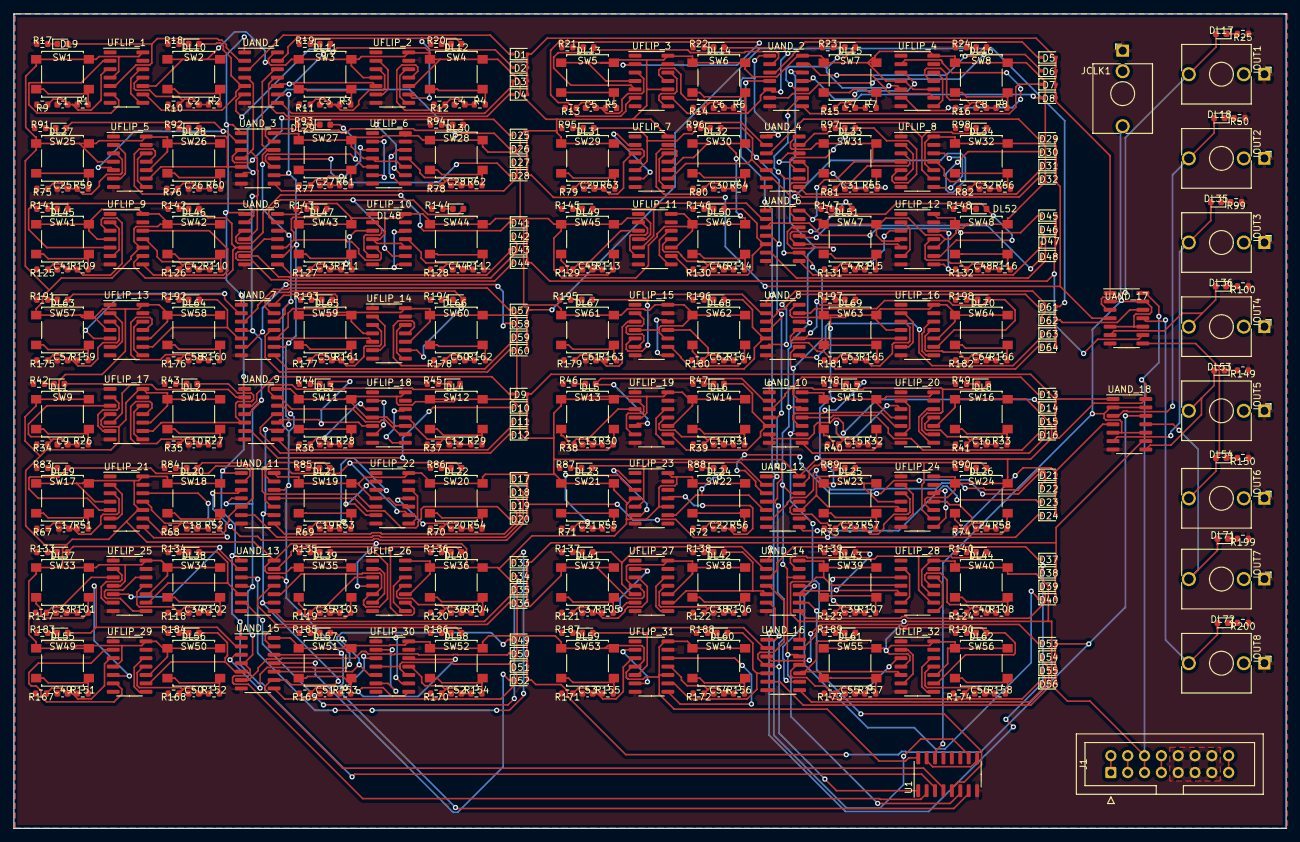
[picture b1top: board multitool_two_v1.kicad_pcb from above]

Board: 2 copper layers, 192.0 x 122.9 mm, 525 parts (0 on the bottom side), 424 nets.

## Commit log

2021-07-06 initial
2021-07-08 committing with a bug
